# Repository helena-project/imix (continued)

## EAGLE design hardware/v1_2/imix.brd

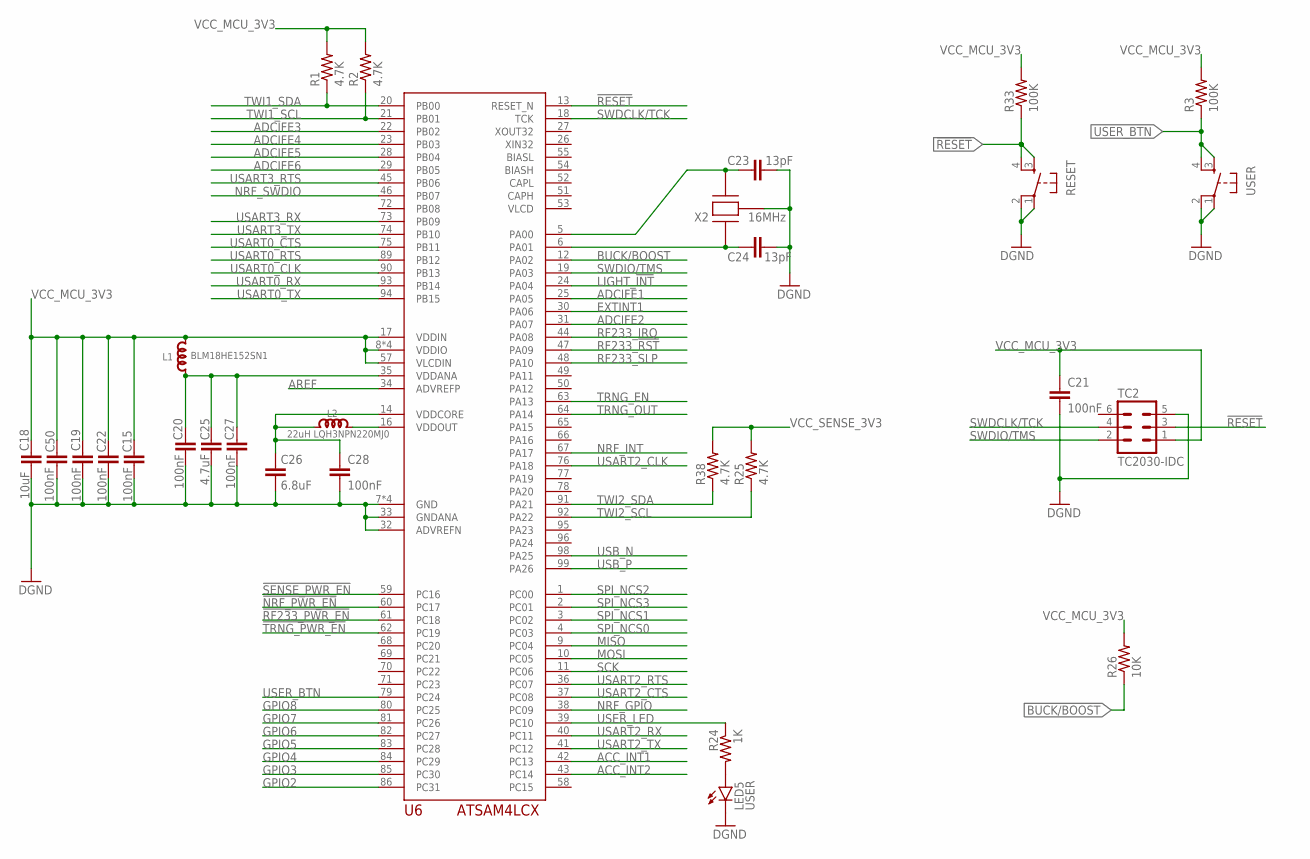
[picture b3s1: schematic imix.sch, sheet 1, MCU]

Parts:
C15, C19, C20, C21, C22, C27, C28, C50: 100nF; C0603
C18: 10uF; C0603
C23, C24: 13pF; C0603
C25: 4.7uF; C0603
C26: 6.8uF; C0603
L1: BLM18HE152SN1; L0603
L2: 22uH LQH3NPN220MJ0; L1212
LED5: USER; LED-0603
R1, R2, R25, R38: 4.7K; 0603-RES
R3, R33: 100K; 0603-RES
R24: 1K; 0603-RES
R26: 10K; 0603-RES
RESET: TAC_SWITCHSMD; TACTILE-SWITCH-SMD
TC2: TC2030-IDC
U6: ATSAM4LCX_100; TQFP100
USER: TAC_SWITCHSMD; TACTILE-SWITCH-SMD
X2: 16MHz; CTS_405_SERIES

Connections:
!NRF_PWR_EN: U6.60 (PC17); also elsewhere on the board
!RESET: R33.1, RESET.3, RESET.4, TC2.3, U6.13 (RESET_N); also elsewhere on the board
!RF233_PWR_EN: U6.61 (PC18); also elsewhere on the board
!SENSE_PWR_EN: U6.59 (PC16); also elsewhere on the board
!TRNG_PWR_EN: U6.62 (PC19); also elsewhere on the board
ACC_INT1: U6.42 (PC13); also elsewhere on the board
ACC_INT2: U6.43 (PC14); also elsewhere on the board
ADCIFE1: U6.25 (PA05); also elsewhere on the board
ADCIFE2: U6.31 (PA07); also elsewhere on the board
ADCIFE3: U6.22 (PB02); also elsewhere on the board
ADCIFE4: U6.23 (PB03); also elsewhere on the board
ADCIFE5: U6.28 (PB04); also elsewhere on the board
ADCIFE6: U6.29 (PB05); also elsewhere on the board
AREF: U6.34 (ADVREFP); also elsewhere on the board
BIASH: U6.54 (BIASH)
BIASL: U6.55 (BIASL)
BUCK/BOOST: R26.1, U6.12 (PA02)
EXTINT1: U6.30 (PA06); also elsewhere on the board
GND: C15.1, C18.1, C19.1, C20.2, C21.2, C22.1, C23.2, C24.2, C25.2, C26.2, C27.2, C28.2, C50.1, LED5.C, RESET.1, RESET.2, TC2.5, U6.7 (GND), U6.15 (GND), U6.32 (ADVREFN), U6.33 (GNDANA), U6.56 (GND), U6.100 (GND), USER.1, USER.2, X2.CASE@2 (CASE), X2.CASE@4 (CASE); also elsewhere on the board
GPIO2: U6.86 (PC31); also elsewhere on the board
GPIO3: U6.85 (PC30); also elsewhere on the board
GPIO4: U6.84 (PC29); also elsewhere on the board
GPIO5: U6.83 (PC28); also elsewhere on the board
GPIO6: U6.82 (PC27); also elsewhere on the board
GPIO7: U6.81 (PC26); also elsewhere on the board
GPIO8: U6.80 (PC25); also elsewhere on the board
LIGHT_!INT: U6.24 (PA04); also elsewhere on the board
MCU_VOUT3.3: L2.2, U6.16 (VDDOUT)
MISO: U6.9 (PC04); also elsewhere on the board
MOSI: U6.10 (PC05); also elsewhere on the board
unnamed: C20.1, C25.1, C27.1, L1.1, U6.35 (VDDANA)
unnamed: C24.1, U6.6 (PA01), X2.1
unnamed: C26.1, C28.1, L2.1, U6.14 (VDDCORE)
unnamed: C23.1, U6.5 (PA00), X2.3 (2)
unnamed: LED5.A, R24.2
NRF_GPIO: U6.38 (PC09); also elsewhere on the board
NRF_INT: U6.67 (PA17); also elsewhere on the board
NRF_SWDIO: U6.46 (PB07); also elsewhere on the board
RF233_!RST: U6.47 (PA09); also elsewhere on the board
RF233_IRQ: U6.44 (PA08); also elsewhere on the board
RF233_SLP: U6.48 (PA10); also elsewhere on the board
SCK: U6.11 (PC06); also elsewhere on the board
SPI_NCS0: U6.4 (PC03); also elsewhere on the board
SPI_NCS1: U6.3 (PC02); also elsewhere on the board
SPI_NCS2: U6.1 (PC00); also elsewhere on the board
SPI_NCS3: U6.2 (PC01); also elsewhere on the board
SWDCLK/TCK: TC2.4, U6.18 (TCK)
SWDIO/TMS: TC2.2, U6.19 (PA03)
TRNG_EN: U6.63 (PA13); also elsewhere on the board
TRNG_OUT: U6.64 (PA14); also elsewhere on the board
TWI1_SCL: R2.1, U6.21 (PB01); also elsewhere on the board
TWI1_SDA: R1.1, U6.20 (PB00); also elsewhere on the board
TWI2_SCL: R25.1, U6.92 (PA22); also elsewhere on the board
TWI2_SDA: R38.1, U6.91 (PA21); also elsewhere on the board
USART0_CLK: U6.90 (PB13); also elsewhere on the board
USART0_CTS: U6.75 (PB11); also elsewhere on the board
USART0_RTS: U6.89 (PB12); also elsewhere on the board
USART0_RX: U6.93 (PB14); also elsewhere on the board
USART0_TX: U6.94 (PB15); also elsewhere on the board
USART2_CLK: U6.76 (PA18); also elsewhere on the board
USART2_CTS: U6.37 (PC08); also elsewhere on the board
USART2_RTS: U6.36 (PC07); also elsewhere on the board
USART2_RX: U6.40 (PC11); also elsewhere on the board
USART2_TX: U6.41 (PC12); also elsewhere on the board
USART3_RTS: U6.45 (PB06); also elsewhere on the board
USART3_RX: U6.73 (PB09); also elsewhere on the board
USART3_TX: U6.74 (PB10); also elsewhere on the board
USB_N: U6.98 (PA25); also elsewhere on the board
USB_P: U6.99 (PA26); also elsewhere on the board
USER_BTN: R3.1, U6.79 (PC24), USER.3, USER.4; also elsewhere on the board
USER_LED: R24.1, U6.39 (PC10); also elsewhere on the board
VCC_MCU_3V3: C15.2, C18.2, C19.2, C21.1, C22.2, C50.2, L1.2, R1.2, R2.2, R3.2, R26.2, R33.2, TC2.1, U6.8 (VDDIO), U6.17 (VDDIN), U6.57 (VLCDIN), U6.87 (VDDIO), U6.88 (VDDIO), U6.97 (VDDIO); also elsewhere on the board
VCC_SENSE_3V3: R25.2, R38.2; also elsewhere on the board

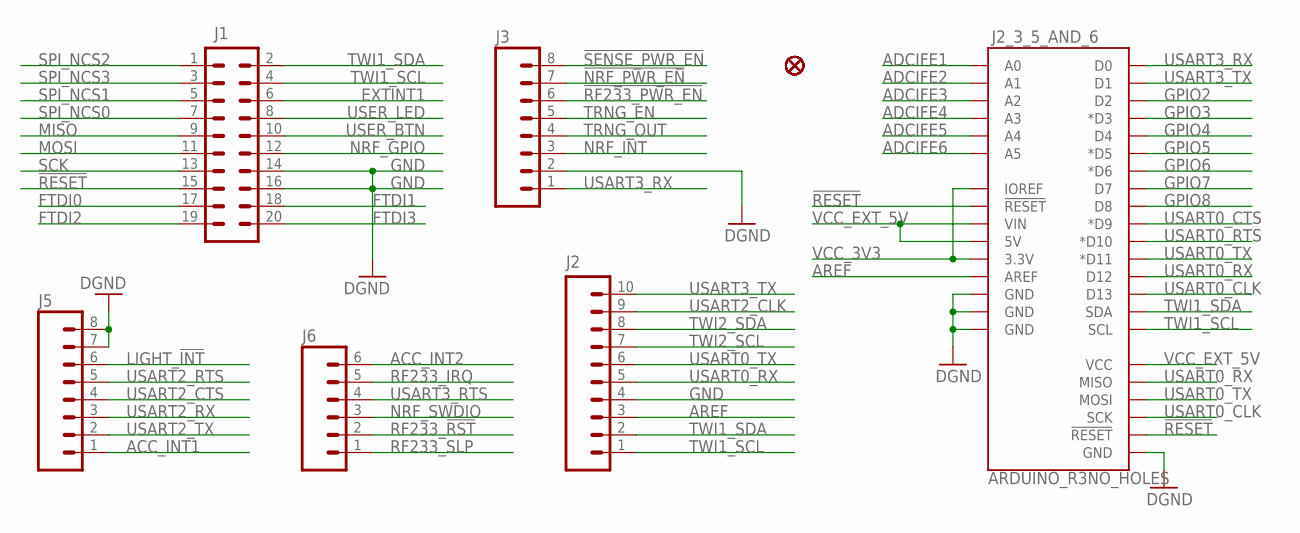
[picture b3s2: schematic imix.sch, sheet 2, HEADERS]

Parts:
F1, F2, F3, F4, F5, F6, F7, F8, F9, F10: FIDUCIAL
J1: M10X2ROUND_NOSILK; 2X10_ROUND_NOSILK
J2: M10NO_SILK_PTH_FEMALE; 1X10_NO_SILK
J2_3_5_AND_6: ARDUINO_R3NO_HOLES; ARDUINO_R3_NO_HOLES
J3, J5: M08NO_SILK_FEMALE_PTH; 1X08_NO_SILK
J6: M06NO_SILK_FEMALE_PTH; 1X06_NO_SILK

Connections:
!NRF_PWR_EN: J3.7; also elsewhere on the board
!RESET: J1.15, J2_3_5_AND_6.RESET@1 (!RESET!), J2_3_5_AND_6.RESET@2 (!RESET!); also elsewhere on the board
!RF233_PWR_EN: J3.6; also elsewhere on the board
!SENSE_PWR_EN: J3.8; also elsewhere on the board
ACC_INT1: J5.1; also elsewhere on the board
ACC_INT2: J6.6; also elsewhere on the board
ADCIFE1: J2_3_5_AND_6.A0; also elsewhere on the board
ADCIFE2: J2_3_5_AND_6.A1; also elsewhere on the board
ADCIFE3: J2_3_5_AND_6.A2; also elsewhere on the board
ADCIFE4: J2_3_5_AND_6.A3; also elsewhere on the board
ADCIFE5: J2_3_5_AND_6.A4; also elsewhere on the board
ADCIFE6: J2_3_5_AND_6.A5; also elsewhere on the board
AREF: J2.3, J2_3_5_AND_6.AREF; also elsewhere on the board
EXTINT1: J1.6; also elsewhere on the board
FTDI0: J1.17; also elsewhere on the board
FTDI1: J1.18; also elsewhere on the board
FTDI2: J1.19; also elsewhere on the board
FTDI3: J1.20; also elsewhere on the board
GND: J1.14, J1.16, J2.4, J2_3_5_AND_6.GND@1 (GND), J2_3_5_AND_6.GND@2 (GND), J2_3_5_AND_6.GND@3 (GND), J2_3_5_AND_6.GND@4 (GND), J3.2, J5.7, J5.8; also elsewhere on the board
GPIO2: J2_3_5_AND_6.D2; also elsewhere on the board
GPIO3: J2_3_5_AND_6.D3 (*D3); also elsewhere on the board
GPIO4: J2_3_5_AND_6.D4; also elsewhere on the board
GPIO5: J2_3_5_AND_6.D5 (*D5); also elsewhere on the board
GPIO6: J2_3_5_AND_6.D6 (*D6); also elsewhere on the board
GPIO7: J2_3_5_AND_6.D7; also elsewhere on the board
GPIO8: J2_3_5_AND_6.D8; also elsewhere on the board
LIGHT_!INT: J5.6; also elsewhere on the board
MISO: J1.9; also elsewhere on the board
MOSI: J1.11; also elsewhere on the board
NRF_GPIO: J1.12; also elsewhere on the board
NRF_INT: J3.3; also elsewhere on the board
NRF_SWDIO: J6.3; also elsewhere on the board
RF233_!RST: J6.2; also elsewhere on the board
RF233_IRQ: J6.5; also elsewhere on the board
RF233_SLP: J6.1; also elsewhere on the board
SCK: J1.13; also elsewhere on the board
SPI_NCS0: J1.7; also elsewhere on the board
SPI_NCS1: J1.5; also elsewhere on the board
SPI_NCS2: J1.1; also elsewhere on the board
SPI_NCS3: J1.3; also elsewhere on the board
TRNG_EN: J3.5; also elsewhere on the board
TRNG_OUT: J3.4; also elsewhere on the board
TWI1_SCL: J1.4, J2.1, J2_3_5_AND_6.SCL; also elsewhere on the board
TWI1_SDA: J1.2, J2.2, J2_3_5_AND_6.SDA; also elsewhere on the board
TWI2_SCL: J2.7; also elsewhere on the board
TWI2_SDA: J2.8; also elsewhere on the board
USART0_CLK: J2_3_5_AND_6.D13, J2_3_5_AND_6.SCK; also elsewhere on the board
USART0_CTS: J2_3_5_AND_6.D9 (*D9); also elsewhere on the board
USART0_RTS: J2_3_5_AND_6.D10 (*D10); also elsewhere on the board
USART0_RX: J2.5, J2_3_5_AND_6.D12, J2_3_5_AND_6.MISO; also elsewhere on the board
USART0_TX: J2.6, J2_3_5_AND_6.D11 (*D11), J2_3_5_AND_6.MOSI; also elsewhere on the board
USART2_CLK: J2.9; also elsewhere on the board
USART2_CTS: J5.4; also elsewhere on the board
USART2_RTS: J5.5; also elsewhere on the board
USART2_RX: J5.3; also elsewhere on the board
USART2_TX: J5.2; also elsewhere on the board
USART3_RTS: J6.4; also elsewhere on the board
USART3_RX: J2_3_5_AND_6.D0, J3.1; also elsewhere on the board
USART3_TX: J2.10, J2_3_5_AND_6.D1; also elsewhere on the board
USER_BTN: J1.10; also elsewhere on the board
USER_LED: J1.8; also elsewhere on the board
VCC_3V3: J2_3_5_AND_6.3.3V, J2_3_5_AND_6.IOREF; also elsewhere on the board
VCC_EXT_5V: J2_3_5_AND_6.5V, J2_3_5_AND_6.VCC, J2_3_5_AND_6.VIN; also elsewhere on the board

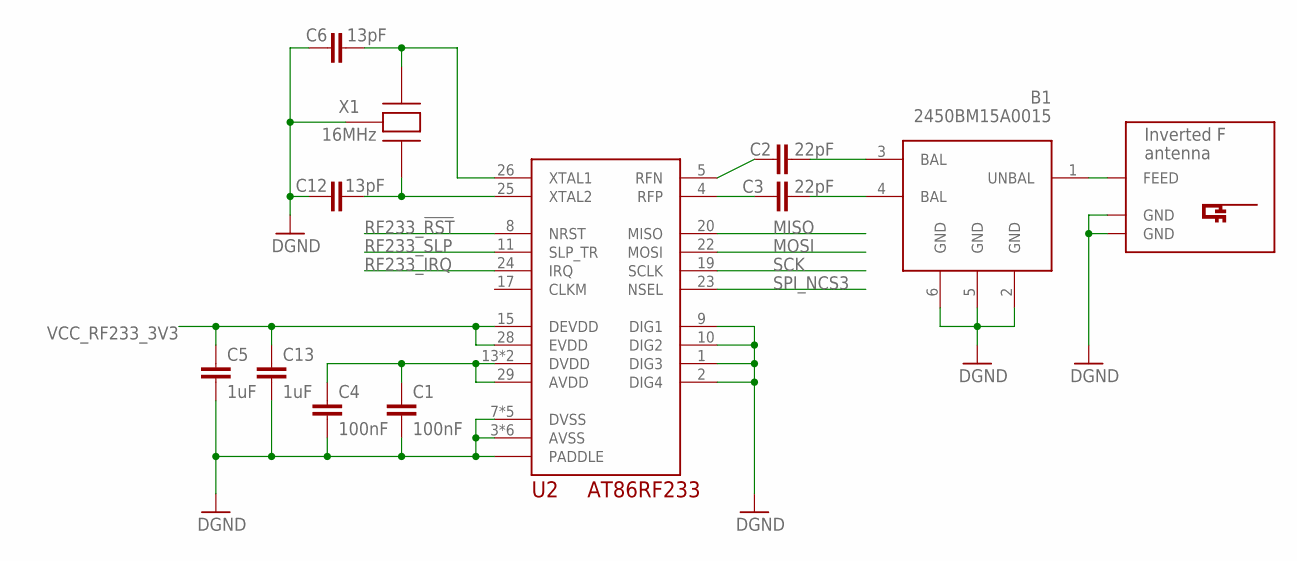
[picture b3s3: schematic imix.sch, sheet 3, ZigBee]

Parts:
B1: 2450BM15A0015; BALUN0805
C1, C4: 100nF; C0603
C2, C3: 22pF; C0603
C5, C13: 1uF; C0603
C6, C12: 13pF; C0603
U2: AT86RF233; 32QN2
U$1: INVERTED_F_ANTENNA-2; DN007-2
X1: 16MHz; CTS_405_SERIES

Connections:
GND: B1.2 (GND), B1.5 (GND), B1.6 (GND), C1.2, C4.2, C5.2, C6.1, C12.1, C13.2, U2.1 (DIG3), U2.2 (DIG4), U2.3 (AVSS), U2.6 (AVSS), U2.7 (DVSS), U2.9 (DIG1), U2.10 (DIG2), U2.12 (DVSS), U2.16 (DVSS), U2.18 (DVSS), U2.21 (DVSS), U2.27 (AVSS), U2.30 (AVSS), U2.31 (AVSS), U2.32 (AVSS), U2.PADDLE, U$1.GND, U$1.GND@1 (GND), X1.CASE@2 (CASE), X1.CASE@4 (CASE); also elsewhere on the board
MISO: U2.20 (MISO); also elsewhere on the board
MOSI: U2.22 (MOSI); also elsewhere on the board
unnamed: C2.2, U2.5 (RFN)
unnamed: C1.1, C4.1, U2.13 (DVDD), U2.14 (DVDD), U2.29 (AVDD)
unnamed: C6.2, U2.26 (XTAL1), X1.1
unnamed: C3.2, U2.4 (RFP)
unnamed: B1.3 (BAL), C2.1
unnamed: C12.2, U2.25 (XTAL2), X1.3 (2)
unnamed: B1.4 (BAL), C3.1
unnamed: B1.1 (UNBAL), U$1.FEED
RF233_!RST: U2.8 (NRST); also elsewhere on the board
RF233_IRQ: U2.24 (IRQ); also elsewhere on the board
RF233_SLP: U2.11 (SLP_TR); also elsewhere on the board
SCK: U2.19 (SCLK); also elsewhere on the board
SPI_NCS3: U2.23 (NSEL); also elsewhere on the board
VCC_RF233_3V3: C5.1, C13.1, U2.15 (DEVDD), U2.28 (EVDD); also elsewhere on the board

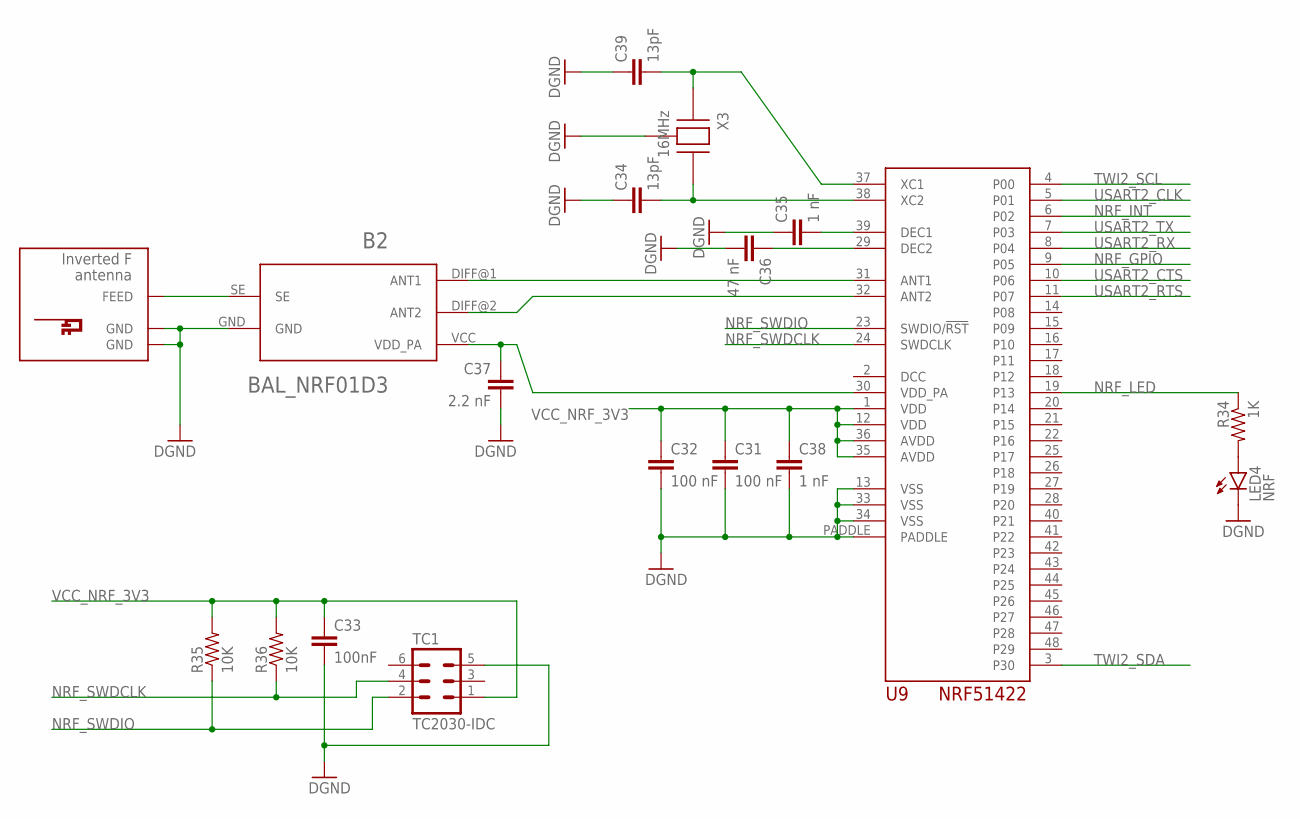
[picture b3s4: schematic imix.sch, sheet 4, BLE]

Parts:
B2: BAL_NRF01D3
C31, C32: 100 nF; C0603
C33: 100nF; C0603
C34, C39: 13pF; C0603
C35, C38: 1 nF; C0603
C36: 47 nF; C0603
C37: 2.2 nF; C0603
LED4: NRF; LED-0603
R34: 1K; 0603-RES
R35, R36: 10K; 0603-RES
TC1: TC2030-IDC
U9: NRF51422; QFN48_6X6
U$4: INVERTED_F_ANTENNA-2; DN007-2
X3: 16MHz; CTS_405_SERIES

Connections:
GND: B2.GND, C31.2, C32.2, C33.2, C34.1, C35.1, C36.2, C37.2, C38.2, C39.1, LED4.C, TC1.5, U9.13 (VSS), U9.33 (VSS), U9.34 (VSS), U9.PADDLE, U$4.GND, U$4.GND@1 (GND), X3.CASE@2 (CASE), X3.CASE@4 (CASE); also elsewhere on the board
unnamed: B2.SE, U$4.FEED
unnamed: B2.VCC (VDD_PA), C37.1, U9.30 (VDD_PA)
unnamed: C34.2, U9.38 (XC2), X3.3 (2)
unnamed: C39.2, U9.37 (XC1), X3.1
unnamed: C35.2, U9.39 (DEC1)
unnamed: C36.1, U9.29 (DEC2)
unnamed: B2.DIFF@1 (ANT1), U9.31 (ANT1)
unnamed: B2.DIFF@2 (ANT2), U9.32 (ANT2)
unnamed: LED4.A, R34.2
NRF_GPIO: U9.9 (P05); also elsewhere on the board
NRF_INT: U9.6 (P02); also elsewhere on the board
NRF_LED: R34.1, U9.19 (P13)
NRF_SWDCLK: R36.1, TC1.4, U9.24 (SWDCLK)
NRF_SWDIO: R35.1, TC1.2, U9.23 (SWDIO/!RST); also elsewhere on the board
TWI2_SCL: U9.4 (P00); also elsewhere on the board
TWI2_SDA: U9.3 (P30); also elsewhere on the board
USART2_CLK: U9.5 (P01); also elsewhere on the board
USART2_CTS: U9.10 (P06); also elsewhere on the board
USART2_RTS: U9.11 (P07); also elsewhere on the board
USART2_RX: U9.8 (P04); also elsewhere on the board
USART2_TX: U9.7 (P03); also elsewhere on the board
VCC_NRF_3V3: C31.1, C32.1, C33.1, C38.1, R35.2, R36.2, TC1.1, U9.1 (VDD), U9.12 (VDD), U9.35 (AVDD), U9.36 (AVDD); also elsewhere on the board

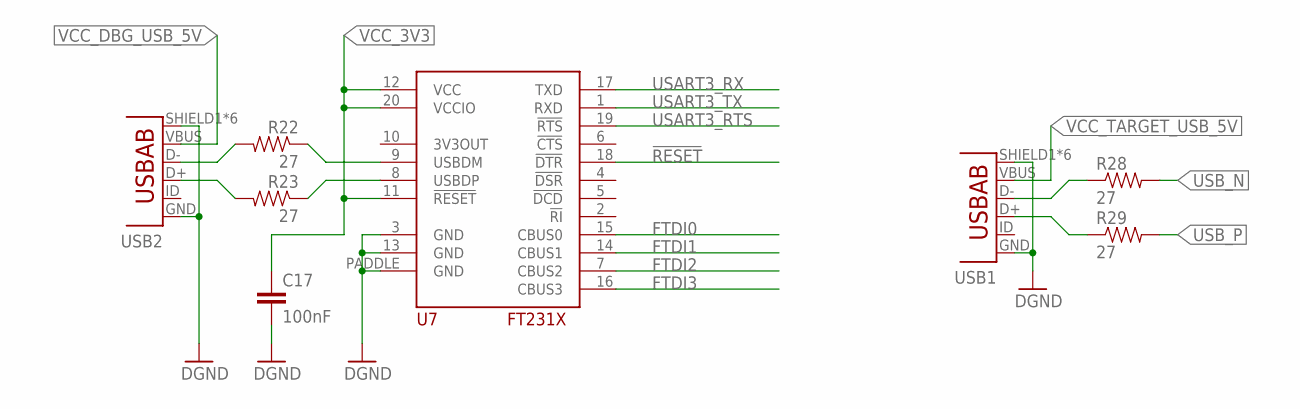
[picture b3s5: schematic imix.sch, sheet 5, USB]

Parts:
C17: 100nF; C0603
R22, R23, R28, R29: 27; 0603-RES
U7: FT231X; QFN20
USB1, USB2: USB-AB; USB-AB-MICRO-SMD

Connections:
!RESET: U7.18 (!DTR); also elsewhere on the board
FTDI0: U7.15 (CBUS0); also elsewhere on the board
FTDI1: U7.14 (CBUS1); also elsewhere on the board
FTDI2: U7.7 (CBUS2); also elsewhere on the board
FTDI3: U7.16 (CBUS3); also elsewhere on the board
GND: C17.2, U7.3 (GND), U7.13 (GND), U7.PADDLE (GND), USB1.GND, USB1.SHIELD1 (SHIELD), USB1.SHIELD2 (SHIELD), USB1.SHIELD3 (SHIELD), USB1.SHIELD4 (SHIELD), USB1.SHIELD5 (SHIELD), USB1.SHIELD6 (SHIELD), USB2.GND, USB2.SHIELD1 (SHIELD), USB2.SHIELD2 (SHIELD), USB2.SHIELD3 (SHIELD), USB2.SHIELD4 (SHIELD), USB2.SHIELD5 (SHIELD), USB2.SHIELD6 (SHIELD); also elsewhere on the board
unnamed: R28.1, USB1.D-
unnamed: R22.2, USB2.D-
unnamed: R22.1, U7.9 (USBDM)
unnamed: R23.2, USB2.D+
unnamed: R23.1, U7.8 (USBDP)
unnamed: R29.1, USB1.D+
USART3_RTS: U7.19 (!RTS); also elsewhere on the board
USART3_RX: U7.17 (TXD); also elsewhere on the board
USART3_TX: U7.1 (RXD); also elsewhere on the board
USB_N: R28.2; also elsewhere on the board
USB_P: R29.2; also elsewhere on the board
VCC_3V3: C17.1, U7.11 (!RESET), U7.12 (VCC), U7.20 (VCCIO); also elsewhere on the board
VCC_DBG_USB_5V: USB2.VBUS; also elsewhere on the board
VCC_TARGET_USB_5V: USB1.VBUS; also elsewhere on the board

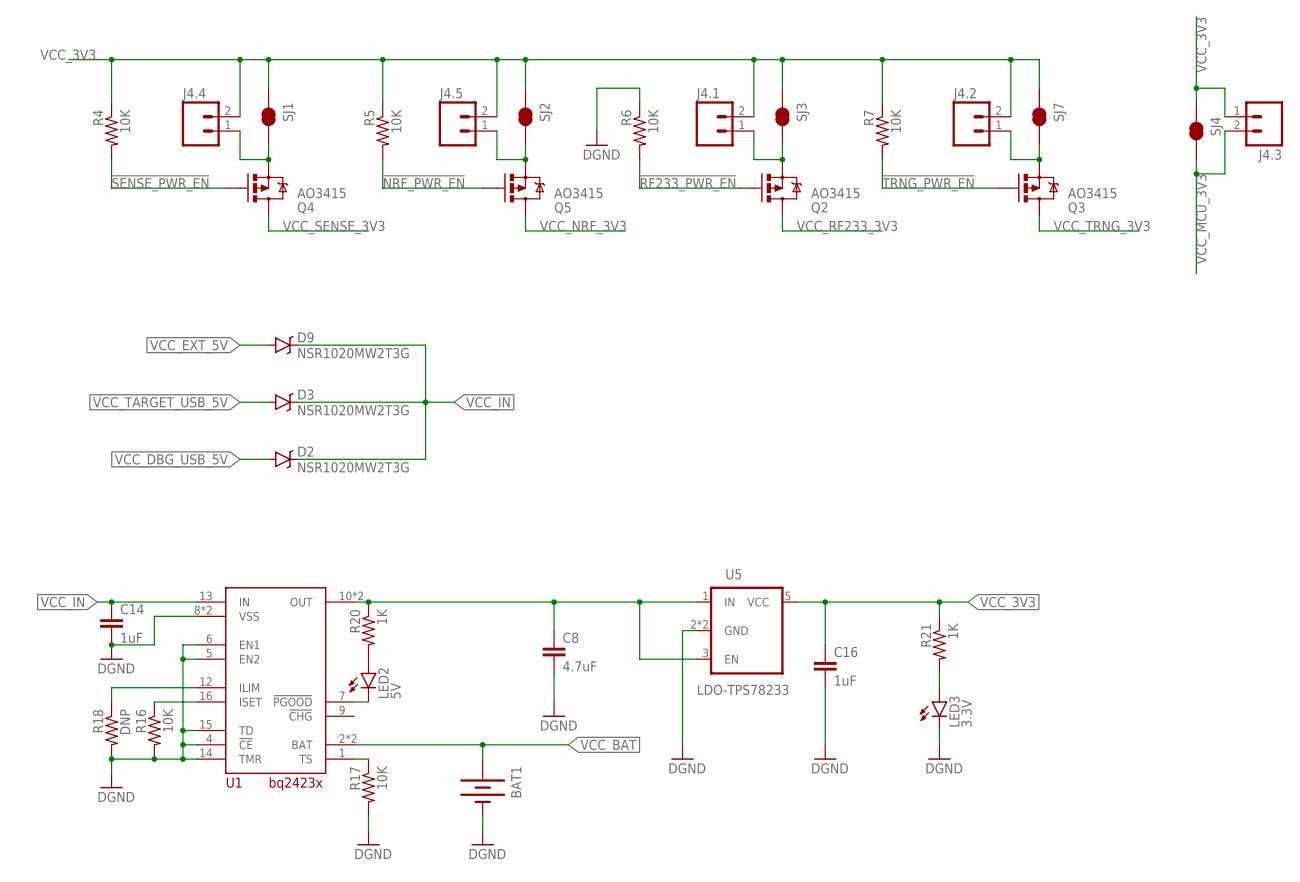
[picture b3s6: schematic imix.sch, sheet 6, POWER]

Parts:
BAT1: BATTERY18650; BATTERY_18650-HOLDER
C8: 4.7uF; C0603
C14, C16: 1uF; C0603
D2, D3, D9: NSR1020MW2T3G; SOD-323
J4.1, J4.2, J4.3, J4.4, J4.5: M02PTH; 1X02
LED2: 5V; LED-0603
LED3: 3.3V; LED-0603
Q2, Q3, Q4, Q5: AO3415; SOT23-3
R4, R5, R6, R7, R16, R17: 10K; 0603-RES
R18: DNP; 0603-RES
R20, R21: 1K; 0603-RES
SJ1, SJ2, SJ3, SJ4, SJ7: JUMPER-PAD-2-NC_BY_TRACE; PAD-JUMPER-2-NC_BY_TRACE_YES_SILK
U1: BQ2423X; QFP16_3X3
U5: LDO-TPS78233; SOT23-5

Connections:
!NRF_PWR_EN: Q5.1 (G), R5.2; also elsewhere on the board
!RF233_PWR_EN: Q2.1 (G), R6.2; also elsewhere on the board
!SENSE_PWR_EN: Q4.1 (G), R4.2; also elsewhere on the board
!TRNG_PWR_EN: Q3.1 (G), R7.2; also elsewhere on the board
GND: BAT1.GND@1 (-), C8.2, C14.2, C16.2, LED3.C, R6.1, R16.2, R17.2, R18.2, U1.4 (!CE), U1.5 (EN2), U1.6 (EN1), U1.8 (VSS), U1.14 (TMR), U1.15 (TD), U1.PAD (VSS), U5.2 (GND), U5.4 (GND); also elsewhere on the board
unnamed: J4.2.1, Q3.2 (S), SJ7.2
unnamed: J4.4.1, Q4.2 (S), SJ1.2
unnamed: J4.5.1, Q5.2 (S), SJ2.2
unnamed: J4.1.1, Q2.2 (S), SJ3.2
unnamed: LED3.A, R21.2
unnamed: LED2.C, U1.7 (!PGOOD)
unnamed: LED2.A, R20.2
unnamed: R17.1, U1.1 (TS)
unnamed: R18.1, U1.12 (ILIM)
unnamed: R16.1, U1.16 (ISET)
VCC_3V3: C16.1, J4.1.2, J4.2.2, J4.3.1, J4.4.2, J4.5.2, R4.1, R5.1, R7.1, R21.1, SJ1.1, SJ2.1, SJ3.1, SJ4.1, SJ7.1, U5.5 (VCC); also elsewhere on the board
VCC_BAT: BAT1.PWR@1 (+), U1.2 (BAT), U1.3 (BAT)
VCC_DBG_USB_5V: D2.A; also elsewhere on the board
VCC_EXT_5V: D9.A; also elsewhere on the board
VCC_IN: C14.1, D2.C, D3.C, D9.C, U1.13 (IN)
VCC_LDO: C8.1, R20.1, U1.10 (OUT), U1.11 (OUT), U5.1 (IN), U5.3 (EN)
VCC_MCU_3V3: J4.3.2, SJ4.2; also elsewhere on the board
VCC_NRF_3V3: Q5.3 (D); also elsewhere on the board
VCC_RF233_3V3: Q2.3 (D); also elsewhere on the board
VCC_SENSE_3V3: Q4.3 (D); also elsewhere on the board
VCC_TARGET_USB_5V: D3.A; also elsewhere on the board
VCC_TRNG_3V3: Q3.3 (D); also elsewhere on the board

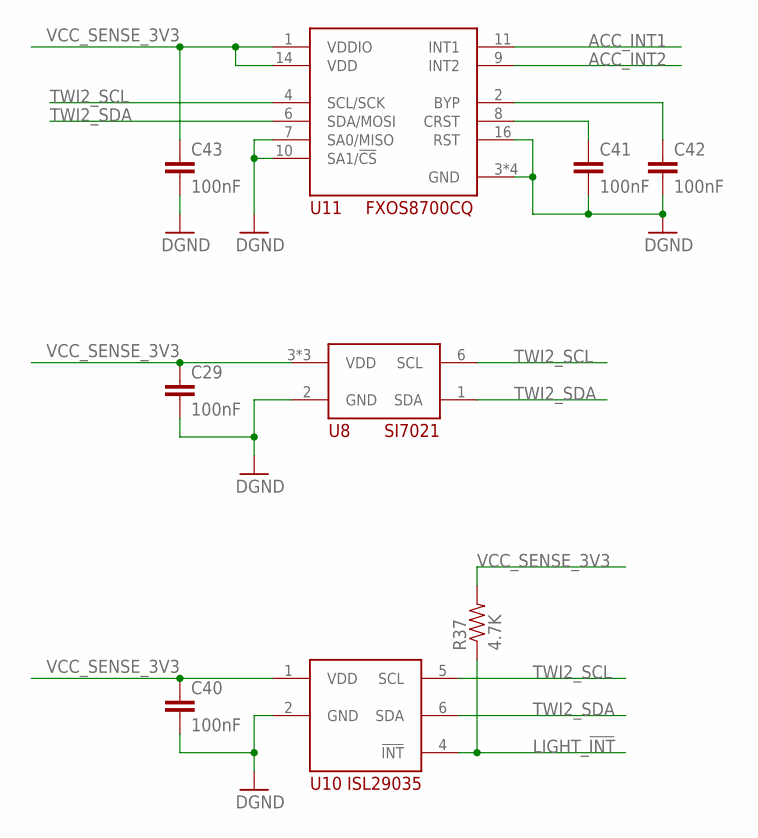
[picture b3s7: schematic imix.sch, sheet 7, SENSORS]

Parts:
C29, C40, C41, C42, C43: 100nF; C0603
R37: 4.7K; 0603-RES
U8: SI7021
U10: ISL29035
U11: FX0S8700CQ; QFN16_3,5

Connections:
ACC_INT1: U11.11 (INT1); also elsewhere on the board
ACC_INT2: U11.9 (INT2); also elsewhere on the board
GND: C29.2, C40.2, C41.2, C42.2, C43.2, U8.2 (GND), U10.2 (GND), U11.3 (GND), U11.5 (GND), U11.7 (SA0/MISO), U11.10 (SA1/!CS), U11.12 (GND), U11.13 (GND), U11.16 (RST); also elsewhere on the board
LIGHT_!INT: R37.1, U10.4 (!INT); also elsewhere on the board
unnamed: C41.1, U11.8 (CRST)
unnamed: C42.1, U11.2 (BYP)
TWI2_SCL: U8.6 (SCL), U10.5 (SCL), U11.4 (SCL/SCK); also elsewhere on the board
TWI2_SDA: U8.1 (SDA), U10.6 (SDA), U11.6 (SDA/MOSI); also elsewhere on the board
VCC_SENSE_3V3: C29.1, C40.1, C43.1, R37.2, U8.3 (VDD), U8.4 (VDD), U8.5 (VDD), U10.1 (VDD), U11.1 (VDDIO), U11.14 (VDD); also elsewhere on the board

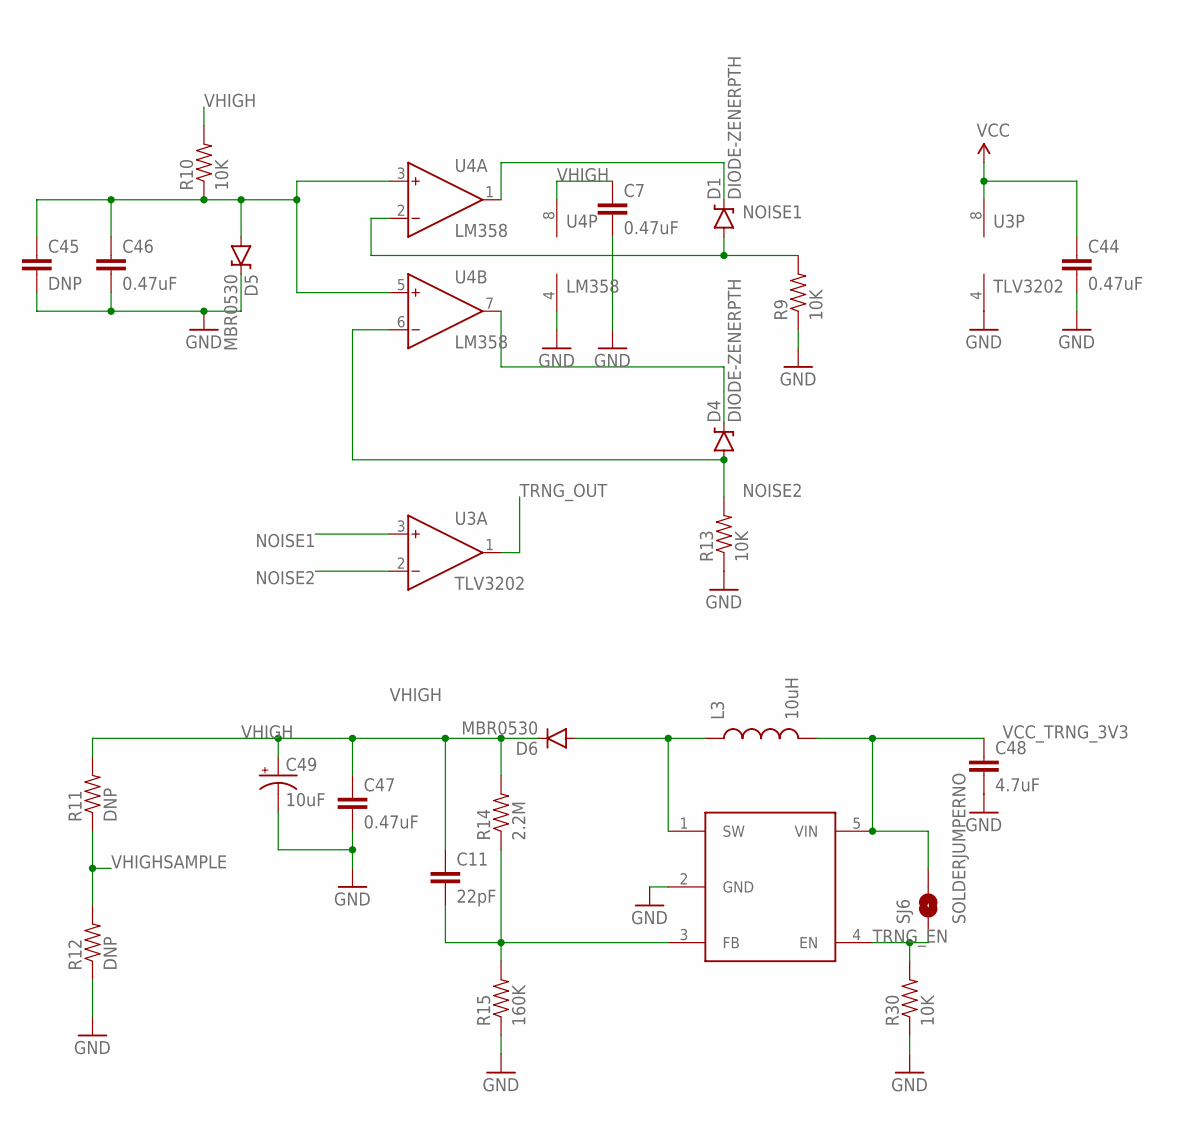
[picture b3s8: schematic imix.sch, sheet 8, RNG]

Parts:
C7, C44, C46, C47: 0.47uF; C0603
C11: 22pF; C0603
C45: DNP; C0603
C48: 4.7uF; C0603
C49: 10uF; PANASONIC_C
D1, D4: DIODE-ZENERPTH; DIODE-ZENER; MPN 610-1N759A
D5, D6: MBR0530; SOD-123
L3: 10uH; 0805
R9, R10, R13, R30: 10K; 0603-RES
R11, R12: DNP; 0603-RES
R14: 2.2M; 0603-RES
R15: 160K; 0603-RES
SJ6: SOLDERJUMPERNO; SJ_2S-NO
U3: TLV3202; SO8
U4: LM358; SO8
U12: 296-12686-1-ND; SOT23-5

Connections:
GND: C7.2, C44.2, C45.2, C46.2, C47.2, C48.2, C49.-, D5.C, R9.1, R12.1, R13.1, R15.1, R30.1, U3.4 (V-), U4.4 (V-), U12.2 (GND); also elsewhere on the board
unnamed: D6.A, L3.1, U12.1 (SW)
unnamed: C11.2, R14.1, R15.2, U12.3 (FB)
unnamed: D1.P$1 (C), U4.1 (OUT)
unnamed: D4.P$1 (C), U4.7 (OUT)
unnamed: C45.1, C46.1, D5.A, R10.1, U4.3 (IN+), U4.5 (IN+)
NOISE1: D1.P$2 (A), R9.2, U3.3 (IN+), U4.2 (IN-)
NOISE2: D4.P$2 (A), R13.2, U3.2 (IN-), U4.6 (IN-)
TRNG_EN: R30.2, SJ6.1, U12.4 (EN); also elsewhere on the board
TRNG_OUT: U3.1 (OUT); also elsewhere on the board
VCC_TRNG_3V3: C44.1, C48.1, L3.2, SJ6.2, U3.8 (V+), U12.5 (VIN); also elsewhere on the board
VHIGH: C7.1, C11.1, C47.1, C49.+, D6.C, R10.2, R11.2, R14.2, U4.8 (V+)
VHIGHSAMPLE: R11.1, R12.2

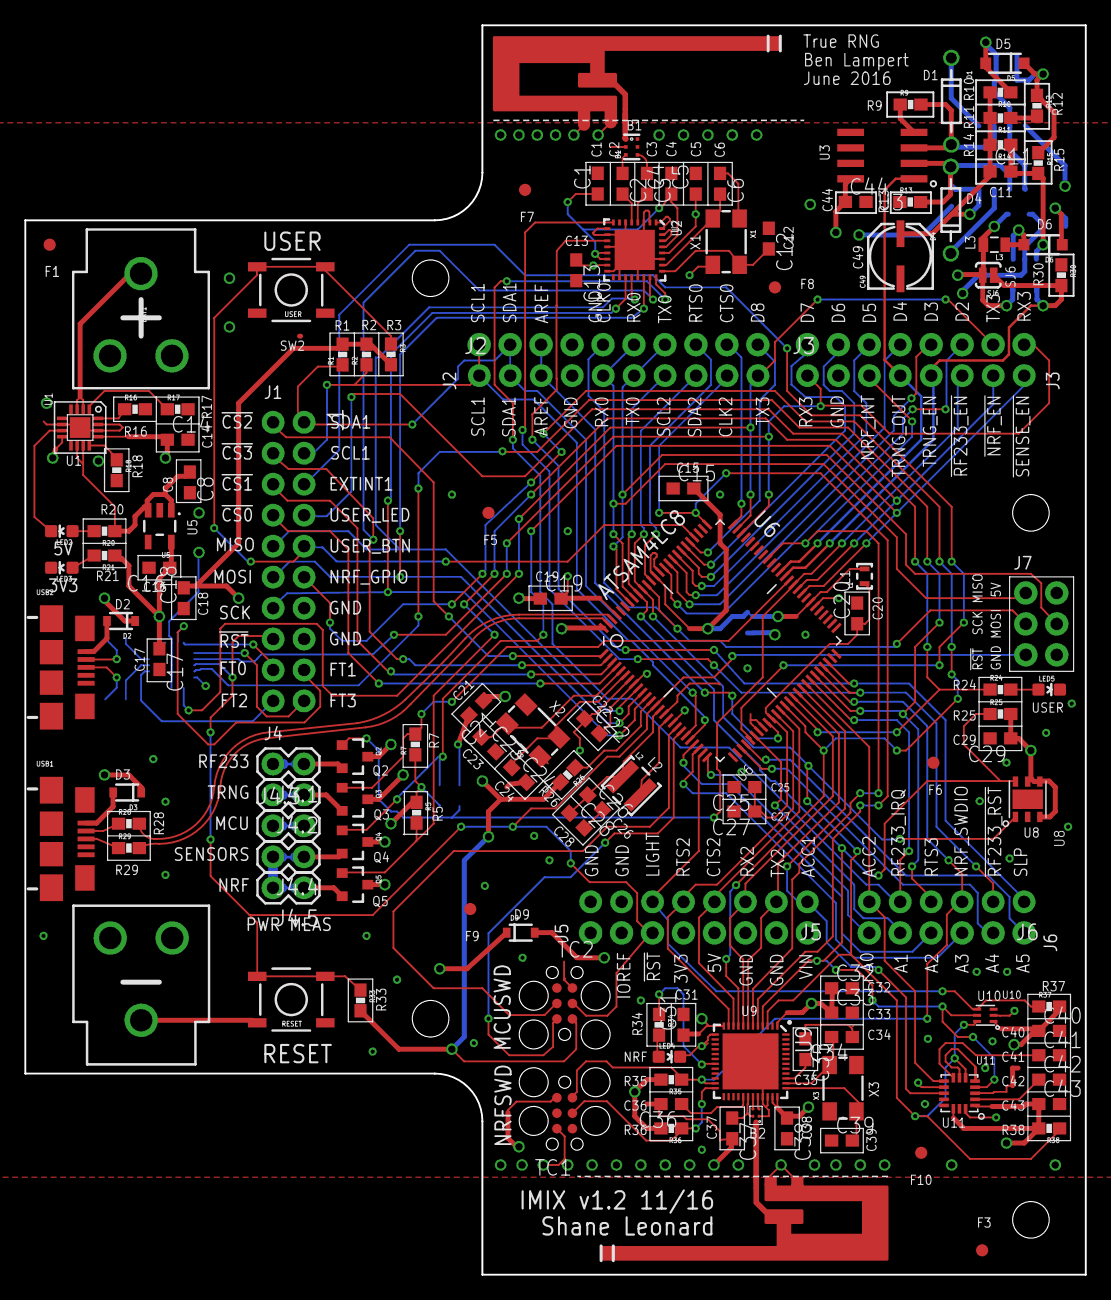
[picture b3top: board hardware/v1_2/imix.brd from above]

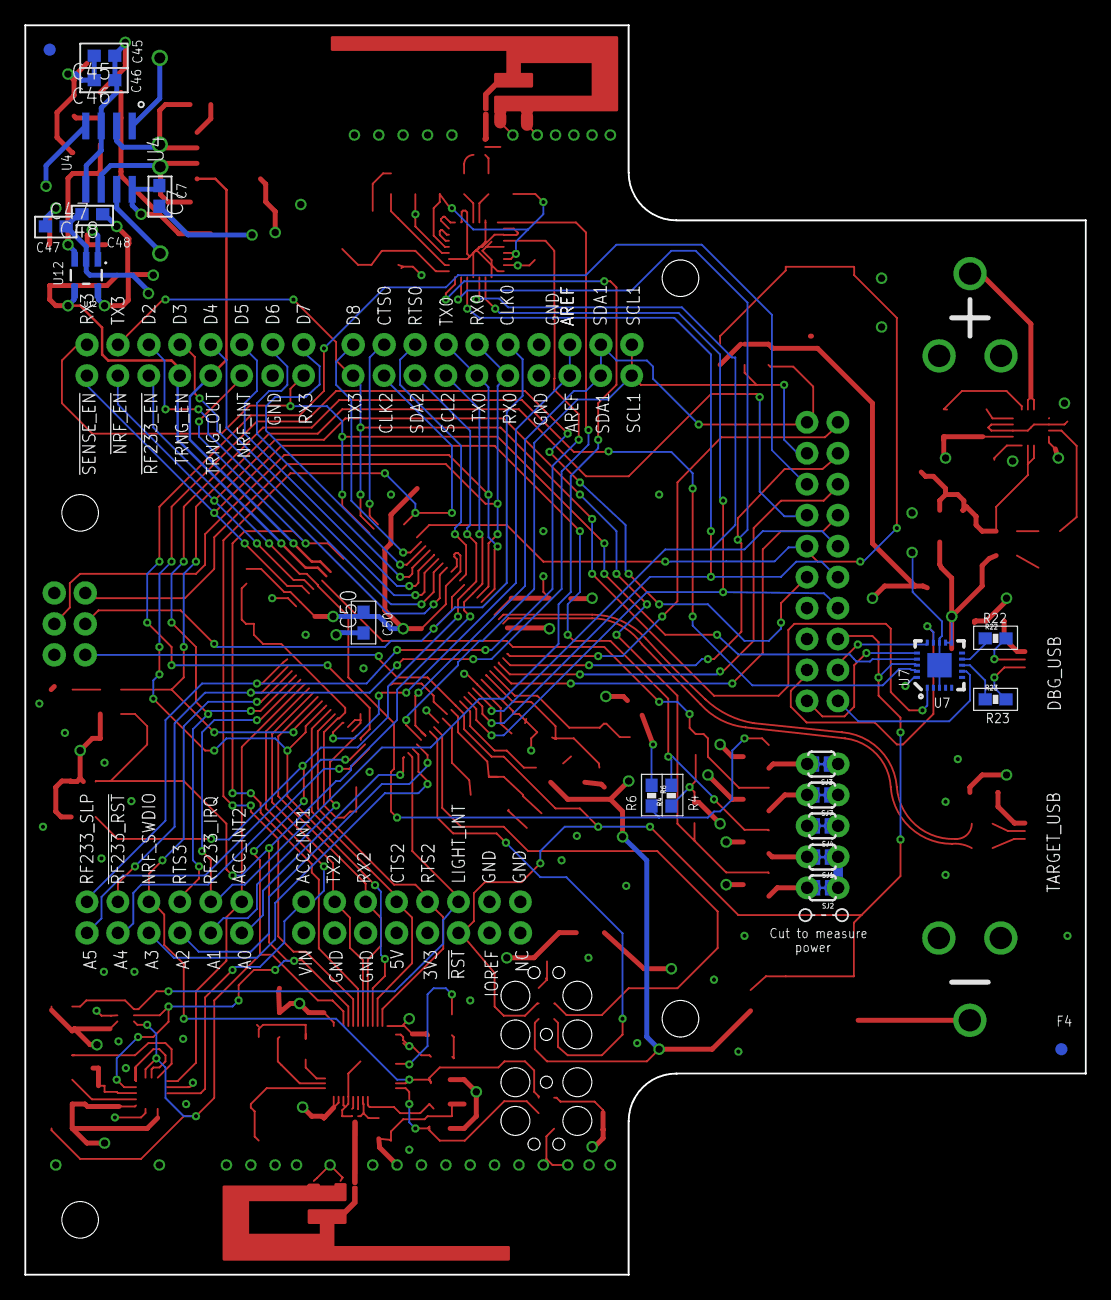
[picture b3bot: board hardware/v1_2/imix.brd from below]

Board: 4 copper layers, 87.0 x 102.5 mm, 151 parts (20 on the bottom side), 131 nets.

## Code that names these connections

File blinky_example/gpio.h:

#ifndef GPIO_H
#define GPIO_H

/* GPIO pin numbering. */
#define PB03 35
#define PA05  5 
#define PA07  7 
#define PA15 15
#define PA16 16
#define PC10 74

/* Functional names for common pins. */
#define USR_LED    PB03
#define USART0_RX  PA05
#define USART0_TX  PA07
#define RNG_EN     PA15
#define RNG_OUT    PA16

#define PERIPH_A   0b000
#define PERIPH_B   0b001
#define PERIPH_C   0b010
#define PERIPH_D   0b011
#define PERIPH_E   0b100
#define PERIPH_F   0b101
#define PERIPH_G   0b110
#define PERIPH_H   0b111

void gpio_enable(int gpio);

void gpio_set_value(int gpio, char value);

void gpio_toggle(int gpio);

void gpio_set_peripheral_function(int gpio, int fn);

#endif // GPIO_H

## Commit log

2016-05-18 Add initial imix schematic
2016-05-18 Add PDF of initial schematic
2016-06-20 Model-T imix, midway complete
2016-06-20 More routing in lower right quadrant
2016-06-29 Progress on routing
2016-06-30 Fully routed and some silkscreen finished
2016-07-03 Top silkscreen nearly complete
2016-07-03 Fix most assembly issues
2016-07-05 Fix reset connection to FTDI
2016-07-05 Update component naming for consistency
2016-07-12 Prototype ready for final review and manufacture
2016-07-13 Update docs
2016-07-13 Move MCU SWD to be accessible when a shield is present
2016-07-13 Update assembly drawings to match repositioned MCU SWD
2016-07-13 Correct USB mislabelling in assembly drawing
2016-07-23 Refactor RNG
2016-07-25 Updated version incorporating several suggestions, still rerouting RNG
2016-07-25 Rearranged RNG
2016-07-26 DFM is almost passing
2016-07-27 Prototype design for v1.0 submitted to fab
2016-08-12 Blinky
2016-08-24 Upload BOM
2016-08-24 Move bom into v1 folder
2016-10-31 Change to NRF51422
2016-10-31 All files for assembly/fab
2016-11-14 Add updated Eagle library
2016-11-14 Updated imix.brd--current with v1.2 Oct 2016
2016-11-14 Updated BOM to include NRF51422 replacement
2016-11-17 Imix lbr includes devices, packages, and symbols now (earlier version only had packages)
2016-11-18 Update misc manufacturing files
2016-11-18 Improve schematic readability and update PDF docs: Fixes #10
2016-11-18 Connect SAM4L pin 8 and 97 to VDDIO and reduce RNG ground plane: addresses #7 and #9
2016-12-20 update readme with image and buy link
2017-02-06 Directory restructure
2017-02-06 Remove CAM files from .gitignore
2017-02-06 Include CAM files from first revisions
2017-02-06 Add 1K resistor b/n FTDI DTR and RESET. Closes #15
2017-02-20 Fix power bugs and other issues in schematic
    * Set EN1 on the battery charger to VCC
    * Replaced the PMOS load switches with SIP32041As
    * Added isolation for the I2C and the RF233 SPI busses
    * Connected the I2C pullups to VCC_MCU, not VCC_SENSE
    * Added resistor between FTDI DTR and RESET (previous commit)
    * Moved power sense headers logically inward towards their power domains
2017-02-20 Create PDF
2017-02-20 Correct 1K resistor quantity in BOM
2017-03-06 Eliminated FabDoc layers and migrated all components to imix library
2017-03-10 Only 19 airwires to go
2017-03-10 Down to 6 airwires
2017-03-10 Down to 3 airwires
2017-03-10 No airwires. Need to run DRC and generate documentation
2017-03-11 Passes DRC
2017-03-11 Rearranged analog pins according to #16
2017-03-12 Correct ADC numbering in doc. Closes #16
2017-03-12 Fab/assembly documentation for v1.3
2017-03-12 Add better cover photo
2017-04-28 Attempts to fix mirrored footprints
2017-05-10 Preautoroute
2017-05-10 One analog switch and all power switches routed
2017-05-10 All elements routed, DRC passes
2017-05-10 Update imix v2.0 schematic pdf
2017-05-10 Update imix v2.0 schematic
2017-07-05 v2.0 quick batch
2017-09-05 imix v2.1 design and documentation
    v2.1 changes:
    * Form factor: now a 2.5"X4" rectangle
    * Removed battery circuit
    * FTDI chip powered correctly for low power
    * Removed unnecessary resistors
    * Renumbered some resistors and capacitors
2017-09-06 Add OSHW logo to silkscreen
2017-10-24 Add commissioning script
2017-10-25 Program imix app on commissioning
2019-11-19 update to version that I got from sawson that actually works
2023-03-02 update submodule to fix svc error on new arm compilers
